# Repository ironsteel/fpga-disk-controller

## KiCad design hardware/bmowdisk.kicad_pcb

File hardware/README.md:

# Floppy disk controller KiCad project based on [BMOW](https://www.bigmessowires.com/) yellowstone card

## Using an iCE40 fpga

For now its just a prototype board with level translators and connectors for an olimex ice40-hx8k dev board

SN74LVC8T245PW symbol used from [gekkio-kicad-libs](https://github.com/Gekkio/gekkio-kicad-libs)

Big thanks to Steve from BMOW for open sourcing his WIP design.

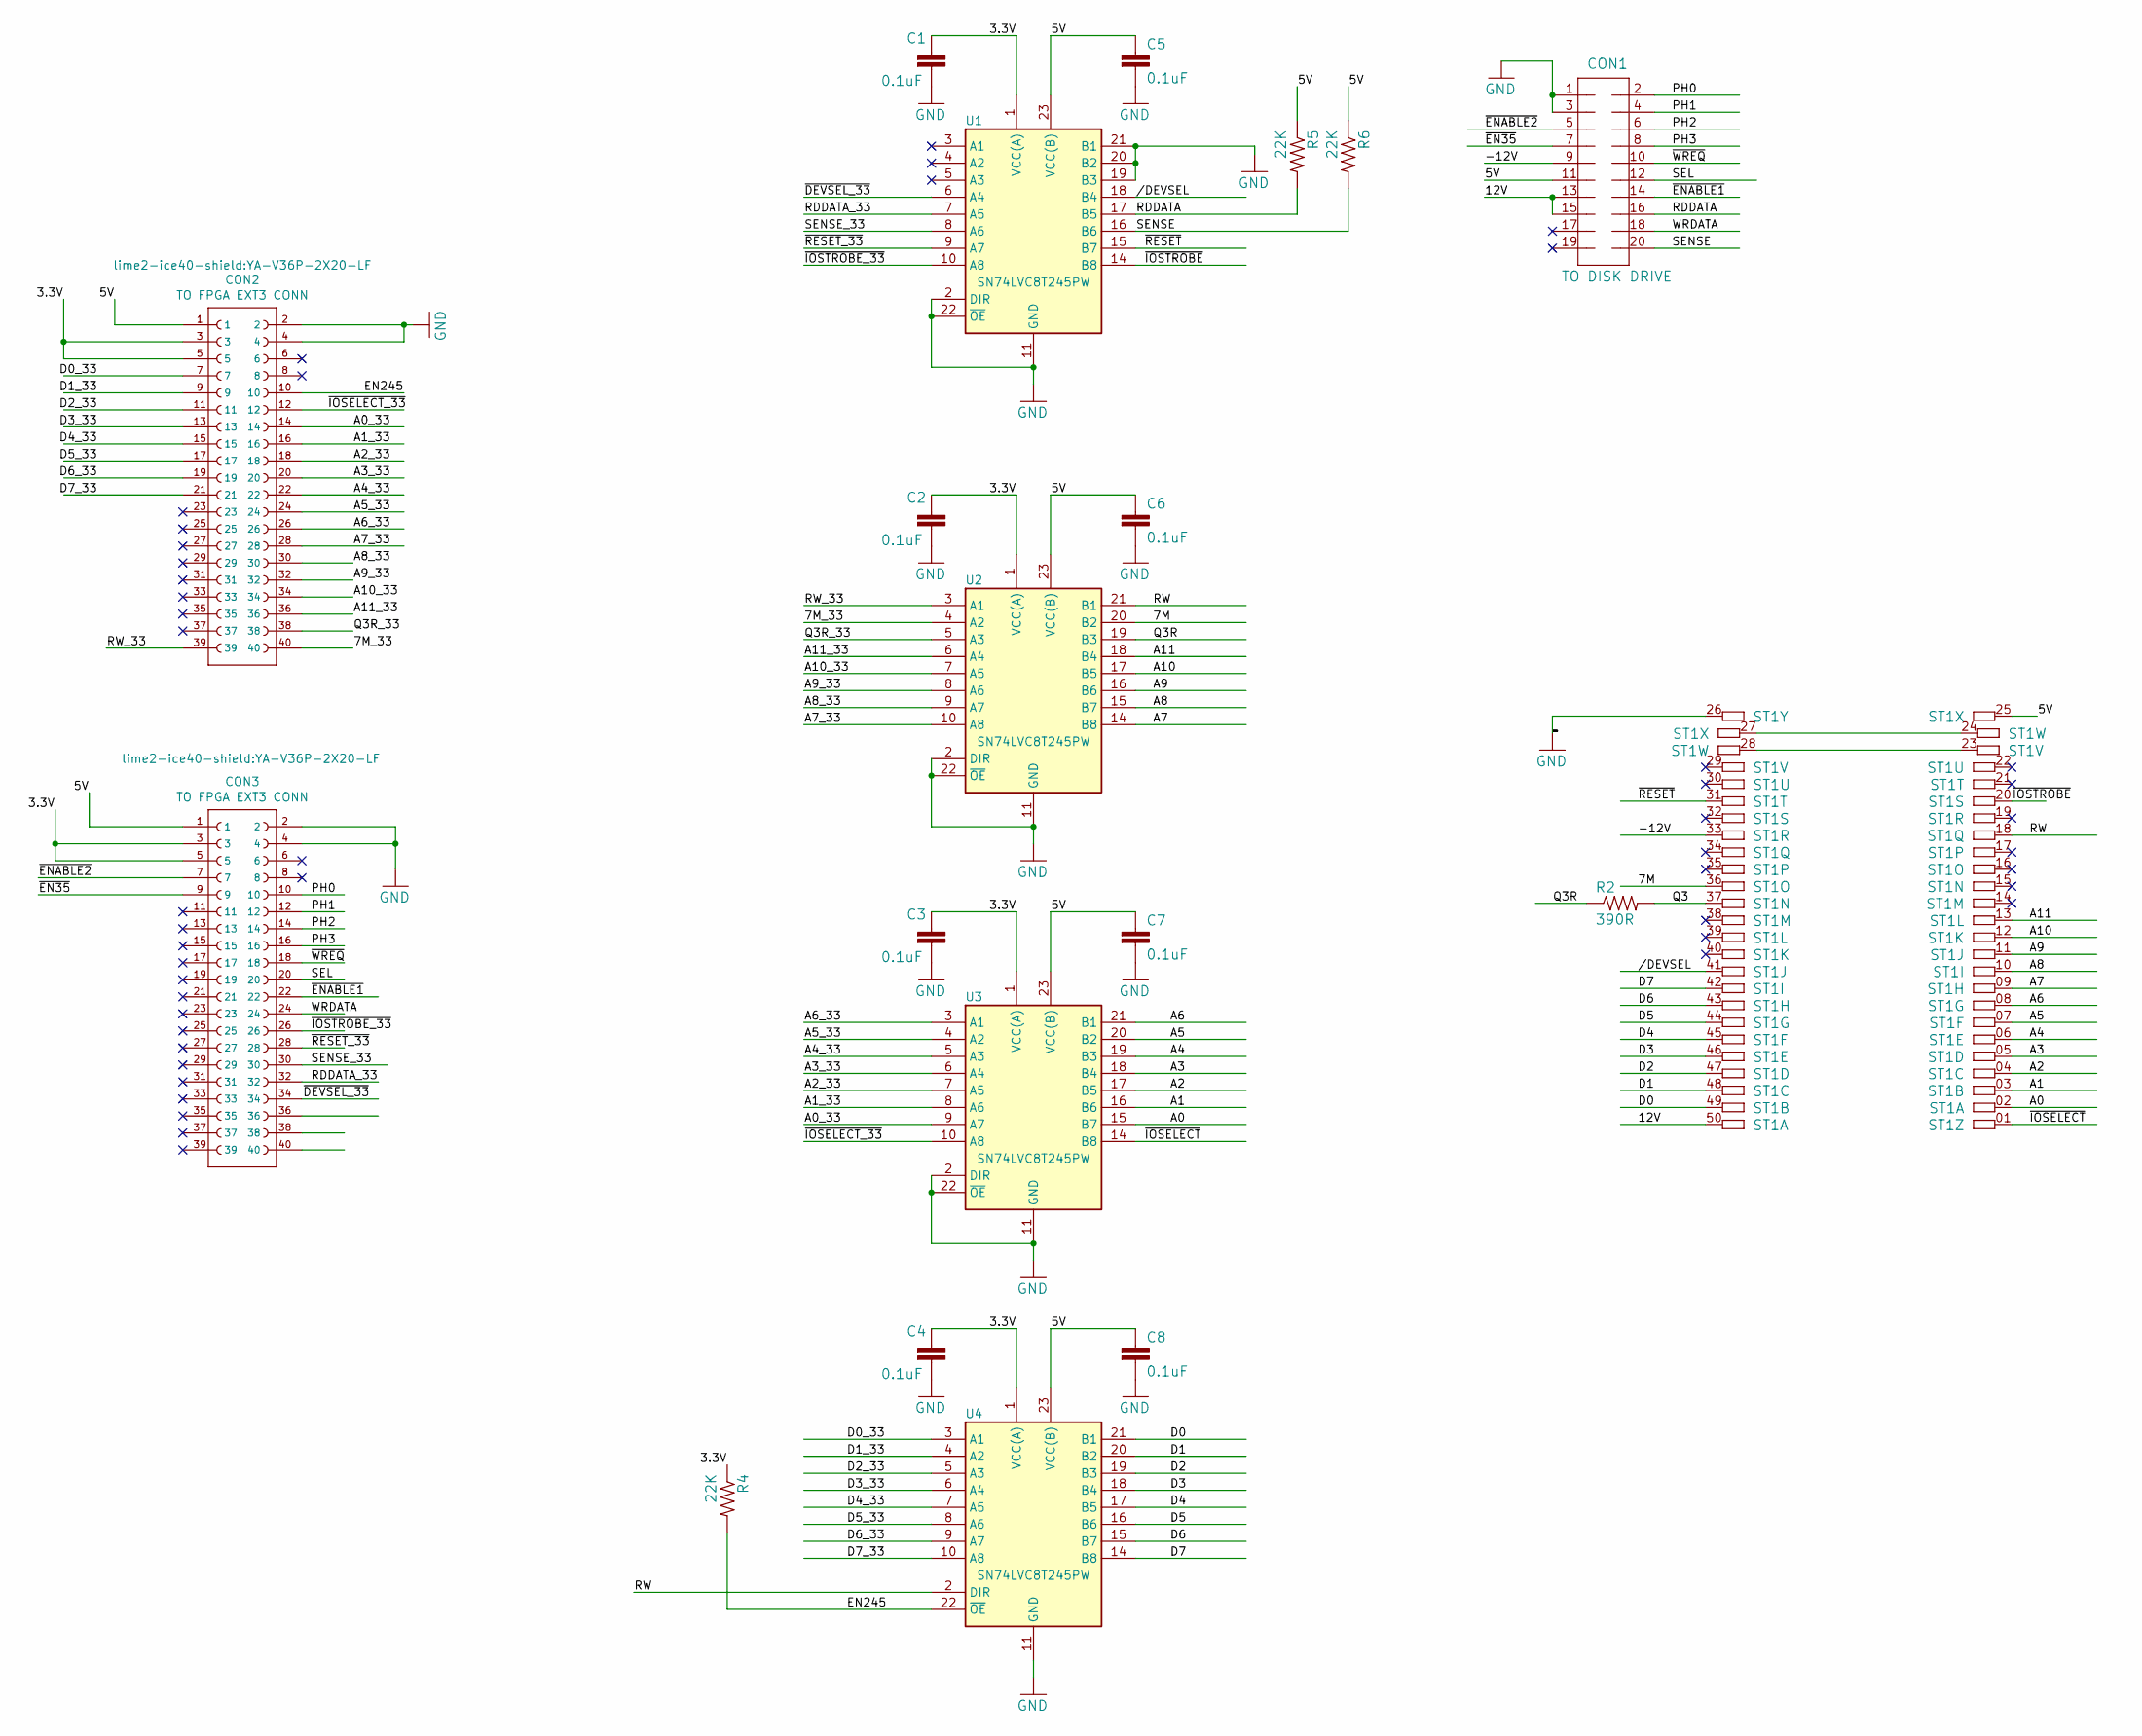
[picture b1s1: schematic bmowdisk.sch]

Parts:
C1, C2, C3, C4, C5, C6, C7, C8: 0.1uF; C_0805_2012Metric_Pad1.18x1.45mm_HandSolder
CON1: TO DISK DRIVE; IDC20
CON2, CON3: TO FPGA EXT3 CONN; YA-V36P-2X20-LF
R2: 390R; R_0805_2012Metric_Pad1.20x1.40mm_HandSolder
R4, R5, R6: 22K; R_0805_2012Metric_Pad1.20x1.40mm_HandSolder
ST1: A2-50PINMINI; A2-50PIN-MINI
U1, U2, U3, U4: SN74LVC8T245PW; TSSOP-24_4.4x7.8mm_P0.65mm

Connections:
/3.3V: C1.1, C2.1, C3.1, C4.1, CON2.3, CON2.5, CON3.3, CON3.5, R4.1, U1.1 (VCC(A)), U2.1 (VCC(A)), U3.1 (VCC(A)), U4.1 (VCC(A))
/5V: C5.1, C6.1, C7.1, C8.1, CON1.11, CON2.1, CON3.1, R5.1, R6.1, ST1.25, U1.23 (VCC(B)), U1.24 (VCC(B)), U2.23 (VCC(B)), U2.24 (VCC(B)), U3.23 (VCC(B)), U3.24 (VCC(B)), U4.23 (VCC(B)), U4.24 (VCC(B))
/7M: ST1.36, U2.20 (B2)
/7M_33: CON2.40, U2.4 (A2)
/12V: CON1.13, CON1.15, ST1.50
/-12V: CON1.9, ST1.33
//DEVSEL: ST1.41, U1.18 (B4)
/A0: ST1.02, U3.15 (B7)
/A0_33: CON2.14, U3.9 (A7)
/A1: ST1.03, U3.16 (B6)
/A1_33: CON2.16, U3.8 (A6)
/A2: ST1.04, U3.17 (B5)
/A2_33: CON2.18, U3.7 (A5)
/A3: ST1.05, U3.18 (B4)
/A3_33: CON2.20, U3.6 (A4)
/A4: ST1.06, U3.19 (B3)
/A4_33: CON2.22, U3.5 (A3)
/A5: ST1.07, U3.20 (B2)
/A5_33: CON2.24, U3.4 (A2)
/A6: ST1.08, U3.21 (B1)
/A6_33: CON2.26, U3.3 (A1)
/A7: ST1.09, U2.14 (B8)
/A7_33: CON2.28, U2.10 (A8)
/A8: ST1.10, U2.15 (B7)
/A8_33: CON2.30, U2.9 (A7)
/A9: ST1.11, U2.16 (B6)
/A9_33: CON2.32, U2.8 (A6)
/A10: ST1.12, U2.17 (B5)
/A10_33: CON2.34, U2.7 (A5)
/A11: ST1.13, U2.18 (B4)
/A11_33: CON2.36, U2.6 (A4)
/D0: ST1.49, U4.21 (B1)
/D0_33: CON2.7, U4.3 (A1)
/D1: ST1.48, U4.20 (B2)
/D1_33: CON2.9, U4.4 (A2)
/D2: ST1.47, U4.19 (B3)
/D2_33: CON2.11, U4.5 (A3)
/D3: ST1.46, U4.18 (B4)
/D3_33: CON2.13, U4.6 (A4)
/D4: ST1.45, U4.17 (B5)
/D4_33: CON2.15, U4.7 (A5)
/D5: ST1.44, U4.16 (B6)
/D5_33: CON2.17, U4.8 (A6)
/D6: ST1.43, U4.15 (B7)
/D6_33: CON2.19, U4.9 (A7)
/D7: ST1.42, U4.14 (B8)
/D7_33: CON2.21, U4.10 (A8)
/EN245: CON2.10, R4.2, U4.22 (~OE)
/PH0: CON1.2, CON3.10
/PH1: CON1.4, CON3.12
/PH2: CON1.6, CON3.14
/PH3: CON1.8, CON3.16
/Q3: R2.2, ST1.37
/Q3R: R2.1, U2.19 (B3)
/Q3R_33: CON2.38, U2.5 (A3)
/RDDATA: CON1.16, R5.2, U1.17 (B5)
/RDDATA_33: CON3.32, U1.7 (A5)
/RW: ST1.18, U2.21 (B1), U4.2 (DIR)
/RW_33: CON2.39, U2.3 (A1)
/SEL: CON1.12, CON3.20
/SENSE: CON1.20, R6.2, U1.16 (B6)
/SENSE_33: CON3.30, U1.8 (A6)
/WRDATA: CON1.18, CON3.24
/~DEVSEL_33: CON3.34, U1.6 (A4)
/~EN35: CON1.7, CON3.9
/~ENABLE1: CON1.14, CON3.22
/~ENABLE2: CON1.5, CON3.7
/~IOSELECT: ST1.01, U3.14 (B8)
/~IOSELECT_33: CON2.12, U3.10 (A8)
/~IOSTROBE: ST1.20, U1.14 (B8)
/~IOSTROBE_33: CON3.26, U1.10 (A8)
/~RESET: ST1.31, U1.15 (B7)
/~RESET_33: CON3.28, U1.9 (A7)
/~WREQ: CON1.10, CON3.18
GND: C1.2, C2.2, C3.2, C4.2, C5.2, C6.2, C7.2, C8.2, CON1.1, CON1.3, CON2.2, CON2.4, CON3.2, CON3.4, ST1.26, U1.2 (DIR), U1.11 (GND), U1.12 (GND), U1.13 (GND), U1.19 (B3), U1.20 (B2), U1.21 (B1), U1.22 (~OE), U2.2 (DIR), U2.11 (GND), U2.12 (GND), U2.13 (GND), U2.22 (~OE), U3.2 (DIR), U3.11 (GND), U3.12 (GND), U3.13 (GND), U3.22 (~OE), U4.11 (GND), U4.12 (GND), U4.13 (GND)
unnamed: ST1.23, ST1.28
unnamed: ST1.24, ST1.27

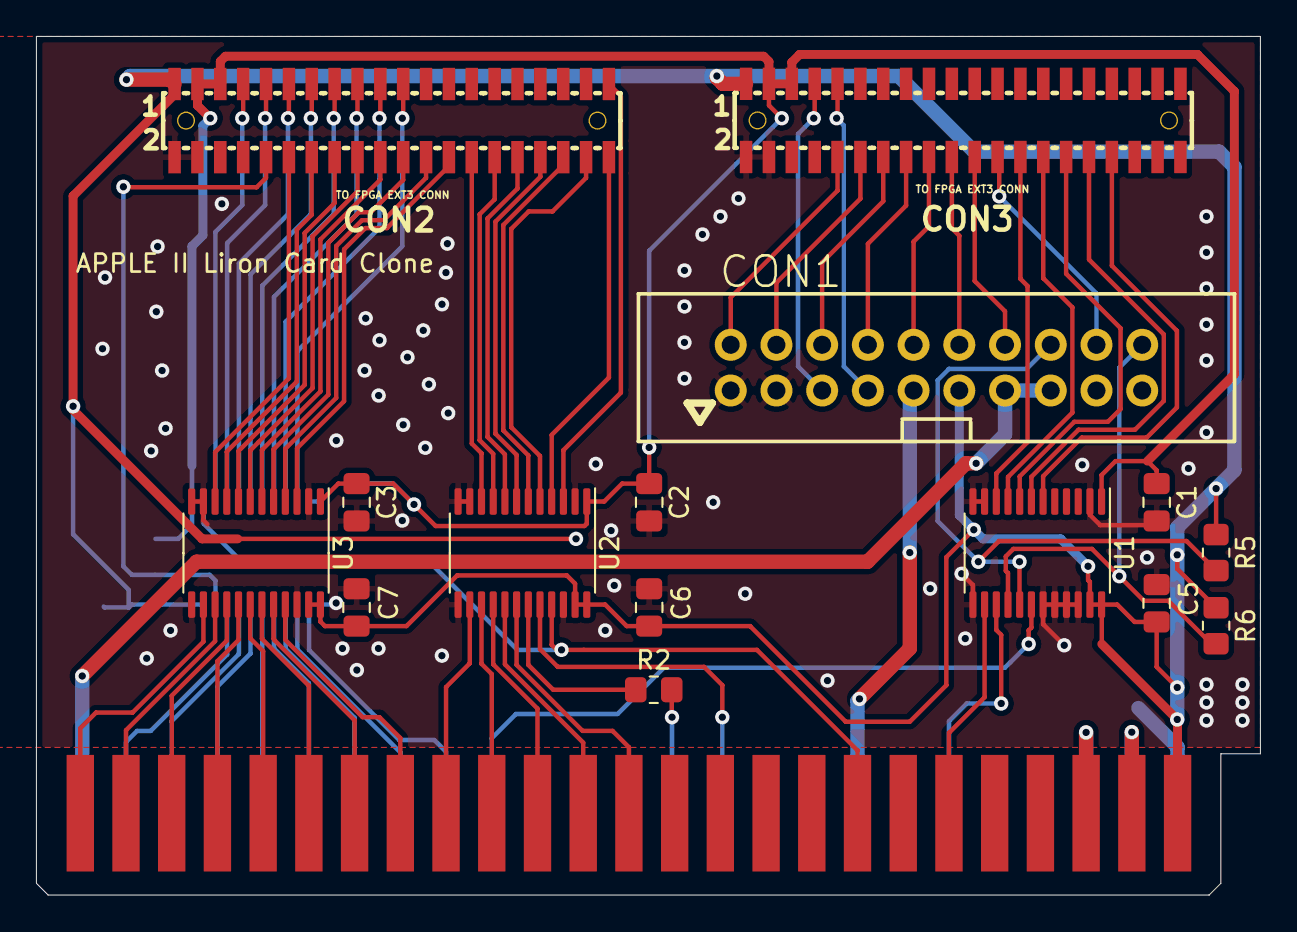
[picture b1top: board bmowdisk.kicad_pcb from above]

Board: 2 copper layers, 68.0 x 47.7 mm, 20 parts (0 on the bottom side), 77 nets.

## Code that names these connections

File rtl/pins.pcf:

set_io clk_100m  J3
set_io addr_in[0]  D15
set_io addr_in[1]  F12
set_io addr_in[2]  F14
set_io addr_in[3]  G12
set_io addr_in[4]  D16
set_io addr_in[5]  G13
set_io addr_in[6]  E16
set_io addr_in[7]  G14
set_io addr_in[8]  F15
set_io addr_in[9]  G11
set_io addr_in[10] F16
set_io addr_in[11] G10

set_io data[0]  M15
set_io data[1]  J11
set_io data[2]  L16
set_io data[3]  K13
set_io data[4]  K14
set_io data[5]  J15
set_io data[6]  K15
set_io data[7]  K16

set_io q3 G15
set_io _reset M6
set_io fclk H12
set_io rw G16
set_io _iosel F11
set_io _iostrobe M3

set_io _en245 E14

set_io phase[0] N4
set_io phase[1] R1
set_io phase[2] M5
set_io phase[3] P2

set_io _wrreq M4
set_io select P1
set_io _enbl1 N3
set_io wrdata L5
set_io sense N2
set_io rddata L7
set_io _devsel M2

set_io _enbl2 C16
set_io _en35 F13

#set_io dbgDataOut[0] E4
#set_io dbgDataOut[1] B2
#set_io dbgDataOut[2] F5
#set_io dbgDataOut[3] B1
#set_io dbgDataOut[4] C1
#set_io dbgDataOut[5] C2
#set_io dbgDataOut[6] F4
#set_io dbgDataOut[7] D2

set_io rx  F3
set_io tx  H3
set_io iostrobe_n G3
set_io iosel_n    E2
set_io devsel_n   H5
set_io bufen    E3
set_io btn    K11

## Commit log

2021-02-07 Convert disk controller eagle project to KiCad
2021-02-17 Tidy up schematics, remove machxo2 FPGA and related components
    Initial prototype version with headers for connecting olimex ice40-hx8k
    fpga dev board for replacing the fpga
2021-02-17 Remove files that should not be tracked in git
2021-02-17 Add readme in hardware dir
2021-02-19 Replace 74X245 with SN74LVC8T245PW
2021-02-19 Add SN74LVC8T245PW datasheet
2021-02-20 Lower text size of labels
    Use ~ for active low labels/signals
    Add TSSOP-24_4.4x7.8mm_P0.65mm footprint to project specific libs
2021-02-20 Change resistor and cap footprints to 0805 for handsoldering
2021-02-21 Place and route board
2021-02-22 Fix connections to 0.05 inch headers
2021-02-22 Remove silk screen from 0.5" headers
    Add text for connections to FPGA board
2021-02-22 conns
2021-02-23 Initial yosys + nextpnr makefile
    Changes to codeROM.v to use yosys block ram inference
2021-03-30 WIP2
2021-05-04 Remove voltage divider for RW line to bus transceiver
